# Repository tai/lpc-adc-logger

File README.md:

# 4-ch ADC Data Logger with LPC1114

This is a simple ADC data logger based on LPC1114FN28 microcontroller.
Primary motivation is to test and record battery runtime independently, without using large/external facility like a PC.

# Major Features
- Can measure voltage of 4 channels every minutes at 10-bit resolution
- Can stream data to serial port
- Can log data to FAT-formatted SD card (saves after every 60 samples)
- Can flush data to SD card with a button press
- Can erase data on SD card with a button press
- Can show activity/response to LEDs
- Supports battery-based, low power operation

# How to Build
```
$ git clone lpc-adc-logger
$ cd lpc-adc-logger
$ platformio lib install 234
$ make
```

# How to Use
- Insert a SD card with a file LOG-0000.DAT on its root folder.
- LOG-0000.DAT must be prepared as a zero-filled file large enough to hold all log data.
-- Command `dd if=/dev/zero of=LOG-0000.DAT bs=1024 count=1024` would do
- Pressing "Erase/Flush" button during powerup erases data in datafile.
- Pressing "Erase/Flush" button during operation flushes data to datafile.
- Connect UART to see a stream of currently sampled data.
- You can power off anytime - however, most recent 512B (1 sector) amount of data will be lost unless flushed by a button press.

# LED pattern meanings
- Fast blink - processing button press
- Slow blink - in operation

# Log File Format

File is written as a series of `logdata_t` data, dumped from memory.
Following is an excerpt from the source code:

```
struct logdata_t {
    uint32_t magic;   //   4B
    uint8_t length;   //   1B
    uint8_t skip[27]; //  27B
    struct {          // 480B
        uint16_t ad[4];
    } sample[60];
} __attribute__((packed));
```

After every 60 samples (of 4ch 16-bit ADC data), this 512B block of
data structure gets full and dumped to the disk. So length is usually
0x3c (decimal 60), but could be less if user has forced to save by
pressing a save button.

LPC1114 is a little-endian ARM Cortex-M0 processor, so beware with the
byte order when accessing multi-byte value.

# Pinouts
- dp1  - SD card (MISO)
- dp2  - SD card (MOSI)
- dp3  - SWD (SWDCLK)
- dp4  - ADC ch#0
- dp5  - NC (reserved for I2C-SDA)
- dp6  - SD card (SCLK)
- dp7  - Analog VCC
- dp8  - Analog GND
- dp9  - ADC ch#1
- dp10 - ADC ch#2
- dp11 - ADC ch#3
- dp12 - SWD (SWDIO)
- dp13 - NC (reserved for PWM/WAKEUP)
- dp14 - Button #1 (Flush/Erase Button)

- dp15 - Serial RX
- dp16 - Serial TX
- dp17 - NC (reserved for button)
- dp18 - NC (reserved for PWM)
- dp19 - NC (XTALOUT)
- dp20 - NC (XTALIN)
- dp21 - VCC
- dp22 - GND
- dp23 - RESET
- dp24 - NC (reserved for CLKOUT)
- dp25 - SD card (SSEL)
- dp26 - LED #1
- dp27 - NC (reserved for I2C-SCL)
- dp28 - NC (reserved for LED #2)

# Schematic

# Notes
- Already functional, but currently under development. 
- Sampling rate is currently 1 sample/s, will make it 1 sample/min in final version.

# See Also
- PlatformIO (https://platformio.org/)
- BlackMagic (https://github.com/blacksphere/blackmagic)
- mBed (https://mbed.org/)
- PFF (http://elm-chan.org/fsw/ff/00index_p.html)
- PinDetect (PlatformIO library #ID: 234)

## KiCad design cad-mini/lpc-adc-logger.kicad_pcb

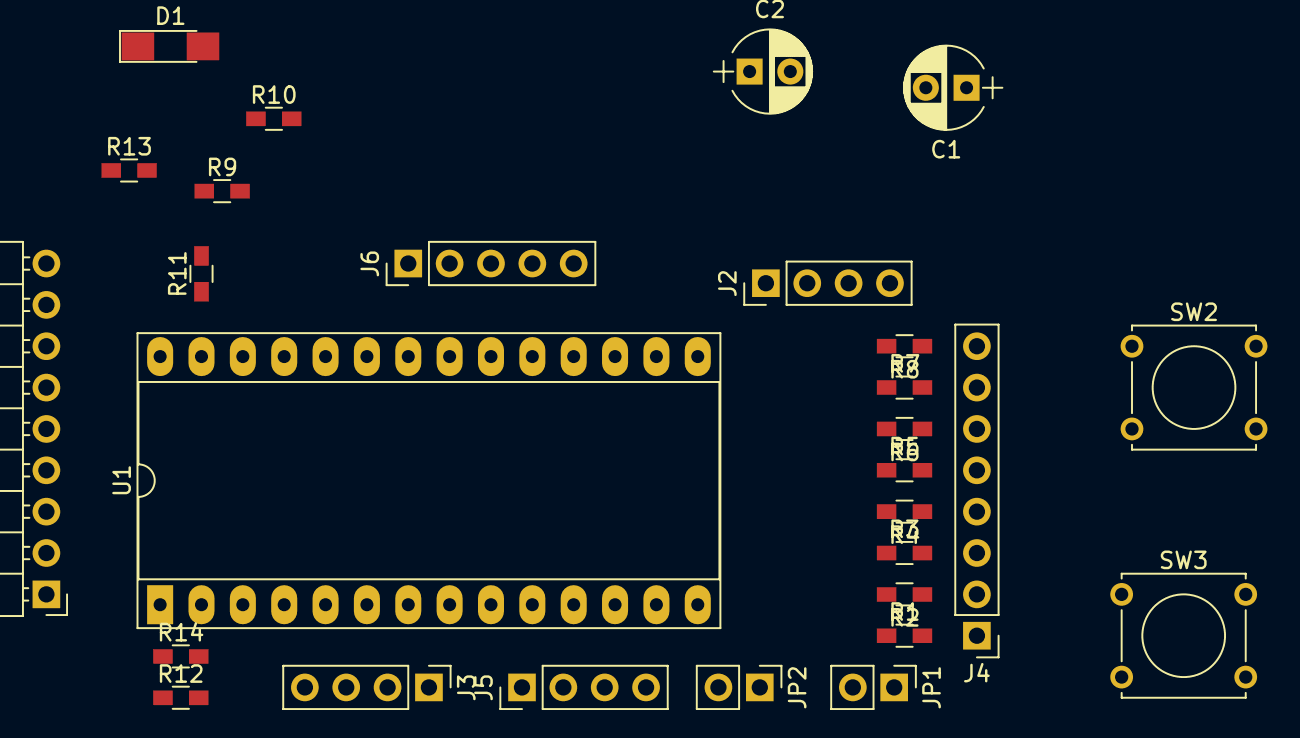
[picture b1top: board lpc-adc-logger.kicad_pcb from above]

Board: 2 copper layers, 28 parts (0 on the bottom side), 29 nets, no tracks yet.

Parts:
C1, C2: 10uF; CP_Radial_D5.0mm_P2.50mm
D1: LED; LED_1206_HandSoldering
J1: SD/SPI; Pin_Header_Angled_1x09_Pitch2.54mm
J2: UART; Pin_Header_Straight_1x04_Pitch2.54mm
J3: I2C; Pin_Header_Straight_1x04_Pitch2.54mm
J4: ANALOG IN; Pin_Header_Straight_1x08_Pitch2.54mm
J5: SWD; Pin_Header_Straight_1x04_Pitch2.54mm
J6: GPIO; Pin_Header_Straight_1x05_Pitch2.54mm
JP1: RATE; Pin_Header_Straight_1x02_Pitch2.54mm
JP2: CARD; Pin_Header_Straight_1x02_Pitch2.54mm
R1, R2, R3, R4, R5, R6, R7, R8, R11, R12: 4.7K; R_0603_HandSoldering
R9: 330; R_0603_HandSoldering
R10: 10K; R_0603_HandSoldering
R13, R14: 47K; R_0603_HandSoldering
SW2: RESET; SW_Tactile_Straight_KSA0Axx1LFTR
SW3: FLUSH; SW_Tactile_Straight_KSA0Axx1LFTR
U1: LPC1114FN28; DIP-28_W15.24mm_Socket_LongPads

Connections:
/CLK: J1.6, U1.6
/CMD/MOSI: J1.3, R14.1, U1.2
/DAT0/MISO: J1.8, R13.1, U1.1
/DAT3/CS: J1.2, U1.25
GND: C1.2, C2.2, J1.4, J1.7, J2.1, J3.1, J4.2, J4.4, J4.6, J4.8, J5.1, J6.1, JP1.1, JP2.1, R2.1, R4.1, R6.1, R8.1, SW2.2, SW3.2, U1.8, U1.22
unnamed: D1.1, U1.28
unnamed: D1.2, R9.1
unnamed: J2.3, U1.16
unnamed: J2.4, U1.15
unnamed: J3.3, R11.1, U1.27
unnamed: J3.4, R12.1, U1.5
unnamed: J4.1, R1.2
unnamed: J4.3, R3.2
unnamed: J4.5, R5.2
unnamed: J4.7, R7.2
unnamed: J5.3, U1.3
unnamed: J5.4, U1.12
unnamed: J6.3, U1.24
unnamed: J6.4, U1.18
unnamed: J6.5, U1.17
unnamed: JP1.2, U1.13
unnamed: JP2.2, U1.14
unnamed: R1.1, R2.2, U1.4
unnamed: R3.1, R4.2, U1.9
unnamed: R5.1, R6.2, U1.10
unnamed: R7.1, R8.2, U1.11
unnamed: R10.1, SW2.1, U1.23
unnamed: SW3.1, U1.26
VCC: C1.1, C2.1, J1.5, J2.2, J3.2, J5.2, J6.2, R9.2, R10.2, R11.2, R12.2, R13.2, R14.2, U1.7, U1.21

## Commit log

2018-05-17 Initial prototype.
2018-05-18 Added basic components
2018-05-18 Moved PFF to lib/
2018-05-18 Moved ProtoThreads to lib/
2018-05-18 Added misc files from platformio.
2018-05-18 Minor doc update.
2018-05-18 Enabled append-logging to SD/FAT.
2018-05-18 Minor doc update
2018-05-18 Explicitly packed logdata_t struct
2018-05-18 Updated data filename to LOG-0000.DAT.
2018-05-18 Added note on file format.
2018-05-18 - Fixed button handling - Added slow/fast LED blink switching
2018-05-18 Minor cleanup
2018-05-18 Improved support for overwrite mode upon startup.
2018-05-18 Fixed logging to work without semihosting.
2018-05-18 Minor update on .gdbinit handling
2018-05-18 Updated sampling interval to 60s.
2018-05-19 Added DAT to CSV converter tool
2018-05-21 Updated schematic.
2018-05-23 Added KiCAD files.
2018-05-23 - Fixed SD card MMC-CS pin - Added GPIO header - Added I2C header
2018-05-24 [WIP] Added SPI header.
2018-11-06 Minor update
2018-11-06 Added kicad design for mini board
2018-11-06 Added LPC1114 datasheet.
